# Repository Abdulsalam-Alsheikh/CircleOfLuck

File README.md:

# Random Number Selector with 12 Segments

This project is an electronic circuit that randomly selects a winner from 12 participants by lighting up the corresponding segment on a circular board. The circuit is built using an Arduino Nano, shift registers, MOSFET transistors, and other components. The design includes a PCB layout, simulation in Proteus, and Arduino code for the logic control.

## Components

- **Arduino Nano**: Controls the entire circuit.
- **2 x 74HC595 Shift Registers**: Expands the number of outputs to control the 12 segments.
- **12 x IRLZ44N MOSFET Transistors**: Used to switch the LEDs for each segment.
- **Resistors**: Various values to limit current and ensure proper operation of the circuit.
- **Power Supply Jack**: To feed the circuit with the required voltage.
- **Junction Connectors**: For connecting each segment to its corresponding transistor.

## Project Files

- **Proteus Simulation File**: A simulation of the circuit to test the functionality before actual implementation **note**( The Arduino code will not work directly here on the simulation due to the adopted method of generating the random number you must change the method of generating the random number before the simulation ) .
- **Arduino Code**: The code used to control the selection process and light up the segments.
- **PCB Design**: A layout of the PCB ready for manufacturing, including all the components and connections.

## Circuit Design

The circuit is designed to randomly select a number from 1 to 12 using an LED on a circular board. The selection is controlled by an Arduino Nano, which sends signals to the shift registers. The shift registers then control the MOSFET transistors, which switch the LEDs on and off based on the random selection.

### How It Works

1. The Arduino generates a random number between 1 and 12.
2. The shift registers receive the number and activate the corresponding MOSFET.
3. The MOSFET then allows current to pass through and lights up the LED corresponding to the selected number.
4. The number remains lit until the process is repeated.

## Usage

1. Load the provided Arduino code into the Arduino Nano.
2. Connect the circuit components as per the schematic in the Proteus file or PCB design.
3. Power the circuit through the power supply jack.
4. The circuit will randomly select a number and light up the corresponding segment.

Watch the final circuit project here [Circuit of CircleOfLuck](https://youtu.be/4vKIFw7FxGo) .
Watch how the circuit logic works here [Logic of CircleOfLuck](https://youtu.be/dwda4XJ68b8) .

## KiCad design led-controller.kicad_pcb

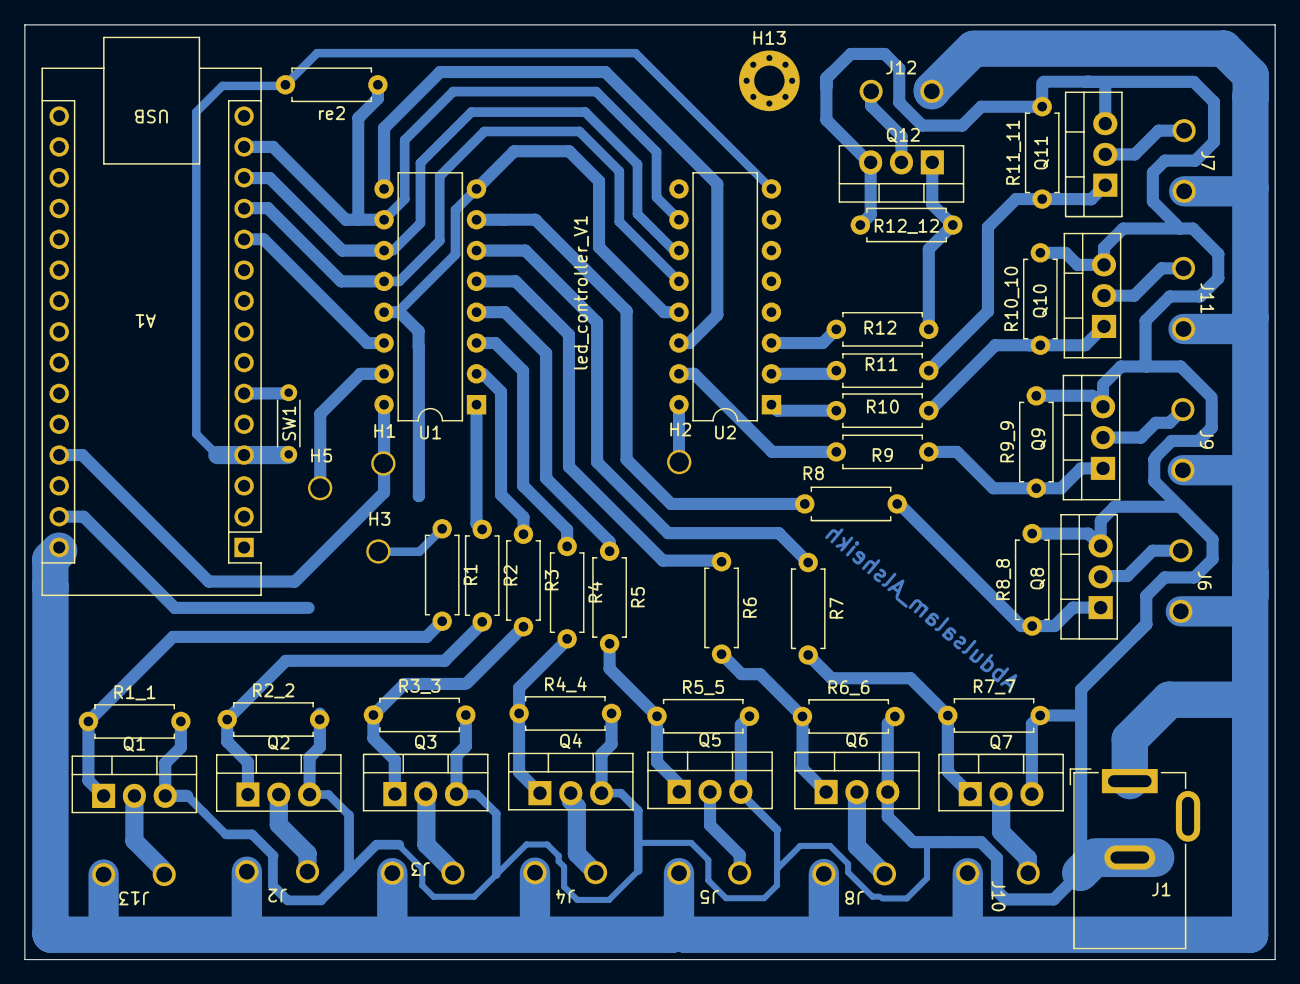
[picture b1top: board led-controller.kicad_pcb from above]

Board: 2 copper layers, 103.1 x 77.0 mm, 59 parts (0 on the bottom side), 45 nets.

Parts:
A1: Arduino_Nano_v3.x; arduino_nano_abd
H1, H2, H3, H5: MountingHole; abd_foot
H13: MountingHole_Pad; MountingHole_2.5mm_Pad_Via
J1: Barrel_Jack_Switch_Pin3Ring; barreljack_10A
J2, J3, J4, J5, J6, J7, J8, J9, J10, J11, J12, J13: Screw_Terminal_01x02; connector borne
Q1, Q2, Q3, Q4, Q5, Q6, Q7, Q8, Q9, Q10, Q11, Q12: IRLZ44N; TO-220-3_Vertical
R1, R2, R3, R4, R5, R6, R7, R8, R9, R10, R11, R12: 220R; R_Axial_DIN0207_L6.3mm_D2.5mm_P7.62mm_Horizontal
R1_1, R2_2, R3_3, R4_4, R5_5, R6_6, R7_7, R8_8, R9_9, R10_10, R11_11, R12_12: 100k; R_Axial_DIN0207_L6.3mm_D2.5mm_P7.62mm_Horizontal
SW1: SW_DIP_x01; R_Axial_DIN0204_L3.6mm_D1.6mm_P5.08mm_Horizontal
U1, U2: 74HC595; DIP-16_W7.62mm
re2: 100k; R_Axial_DIN0207_L6.3mm_D2.5mm_P7.62mm_Horizontal

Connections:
/1: R1.1, U1.15 (QA)
/2: R2.1, U1.1 (QB)
/3: R3.1, U1.2 (QC)
/4: R4.1, U1.3 (QD)
/5: R5.1, U1.4 (QE)
/6: R6.1, U1.5 (QF)
/7: R7.1, U1.6 (QG)
/8: R8.1, U1.7 (QH)
/9: R9.1, U2.15 (QA)
/10: R10.1, U2.1 (QB)
/11: R11.1, U2.2 (QC)
/12: R12.1, U2.3 (QD)
/+12V: A1.30 (VIN), J1.1, J2.1, J3.1, J4.1, J5.1, J6.1, J7.1, J8.1, J9.1, J10.1, J11.1, J12.1, J13.1
/gnd1: A1.4 (GND), A1.29 (GND), J1.2, Q1.3 (S), Q2.3 (S), Q3.3 (S), Q4.3 (S), Q5.3 (S), Q6.3 (S), Q7.3 (S), Q8.3 (S), Q9.3 (S), Q10.3 (S), Q11.3 (S), Q12.3 (S), R1_1.2, R2_2.2, R3_3.2, R4_4.2, R5_5.2, R6_6.2, R7_7.2, R8_8.2, R9_9.2, R10_10.2, R11_11.2, R12_12.2, SW1.1, U1.8 (GND), U1.13 (~OE), U2.8 (GND), U2.13 (~OE), re2.2
/swich: A1.6 (D3), SW1.2
unnamed: A1.11 (D8), U1.14 (SER)
unnamed: A1.12 (D9), U1.12 (RCLK), U2.12 (RCLK)
unnamed: A1.13 (D10), U1.11 (SRCLK), U2.11 (SRCLK)
unnamed: A1.14 (D11), U1.10 (~SRCLR), U2.10 (~SRCLR), re2.1
unnamed: A1.27 (+5V), U1.16 (VCC), U2.16 (VCC)
unnamed: J2.2, Q2.2 (D)
unnamed: J3.2, Q3.2 (D)
unnamed: J4.2, Q4.2 (D)
unnamed: J5.2, Q5.2 (D)
unnamed: J6.2, Q8.2 (D)
unnamed: J7.2, Q11.2 (D)
unnamed: J8.2, Q6.2 (D)
unnamed: J9.2, Q9.2 (D)
unnamed: J10.2, Q7.2 (D)
unnamed: J11.2, Q10.2 (D)
unnamed: J12.2, Q12.2 (D)
unnamed: J13.2, Q1.2 (D)
unnamed: Q1.1 (G), R1.2, R1_1.1
unnamed: Q2.1 (G), R2.2, R2_2.1
unnamed: Q3.1 (G), R3.2, R3_3.1
unnamed: Q4.1 (G), R4.2, R4_4.1
unnamed: Q5.1 (G), R5.2, R5_5.1
unnamed: Q6.1 (G), R6.2, R6_6.1
unnamed: Q7.1 (G), R7.2, R7_7.1
unnamed: Q8.1 (G), R8.2, R8_8.1
unnamed: Q9.1 (G), R9.2, R9_9.1
unnamed: Q10.1 (G), R10.2, R10_10.1
unnamed: Q11.1 (G), R11.2, R11_11.1
unnamed: Q12.1 (G), R12.2, R12_12.1
unnamed: U1.9 (QH'), U2.14 (SER)

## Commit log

2024-08-13 Rename led-controller.kicad_pro to KiCad_Project.kicad_pro
2024-08-13 Rename last_design.pdsprj to Proteus_Simulation.pdsprj
